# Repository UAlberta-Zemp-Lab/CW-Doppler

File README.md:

### Continuous Wave Doppler
--- 
Code and board files for high voltage switch and Teensy firmware

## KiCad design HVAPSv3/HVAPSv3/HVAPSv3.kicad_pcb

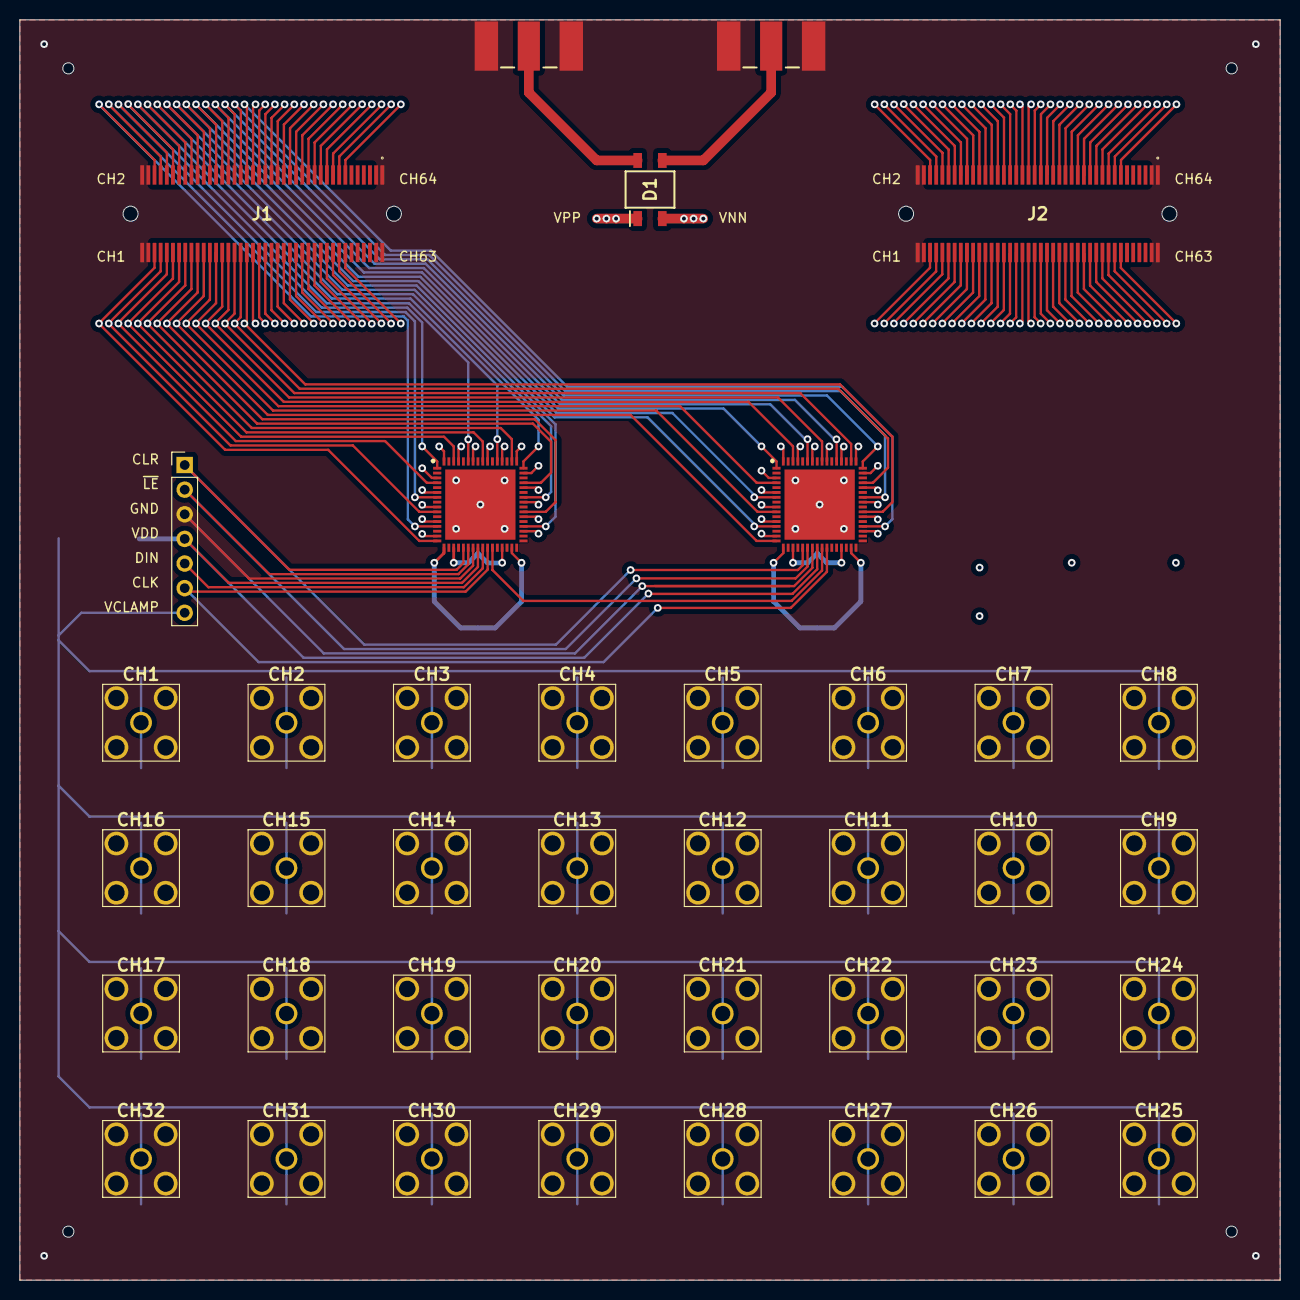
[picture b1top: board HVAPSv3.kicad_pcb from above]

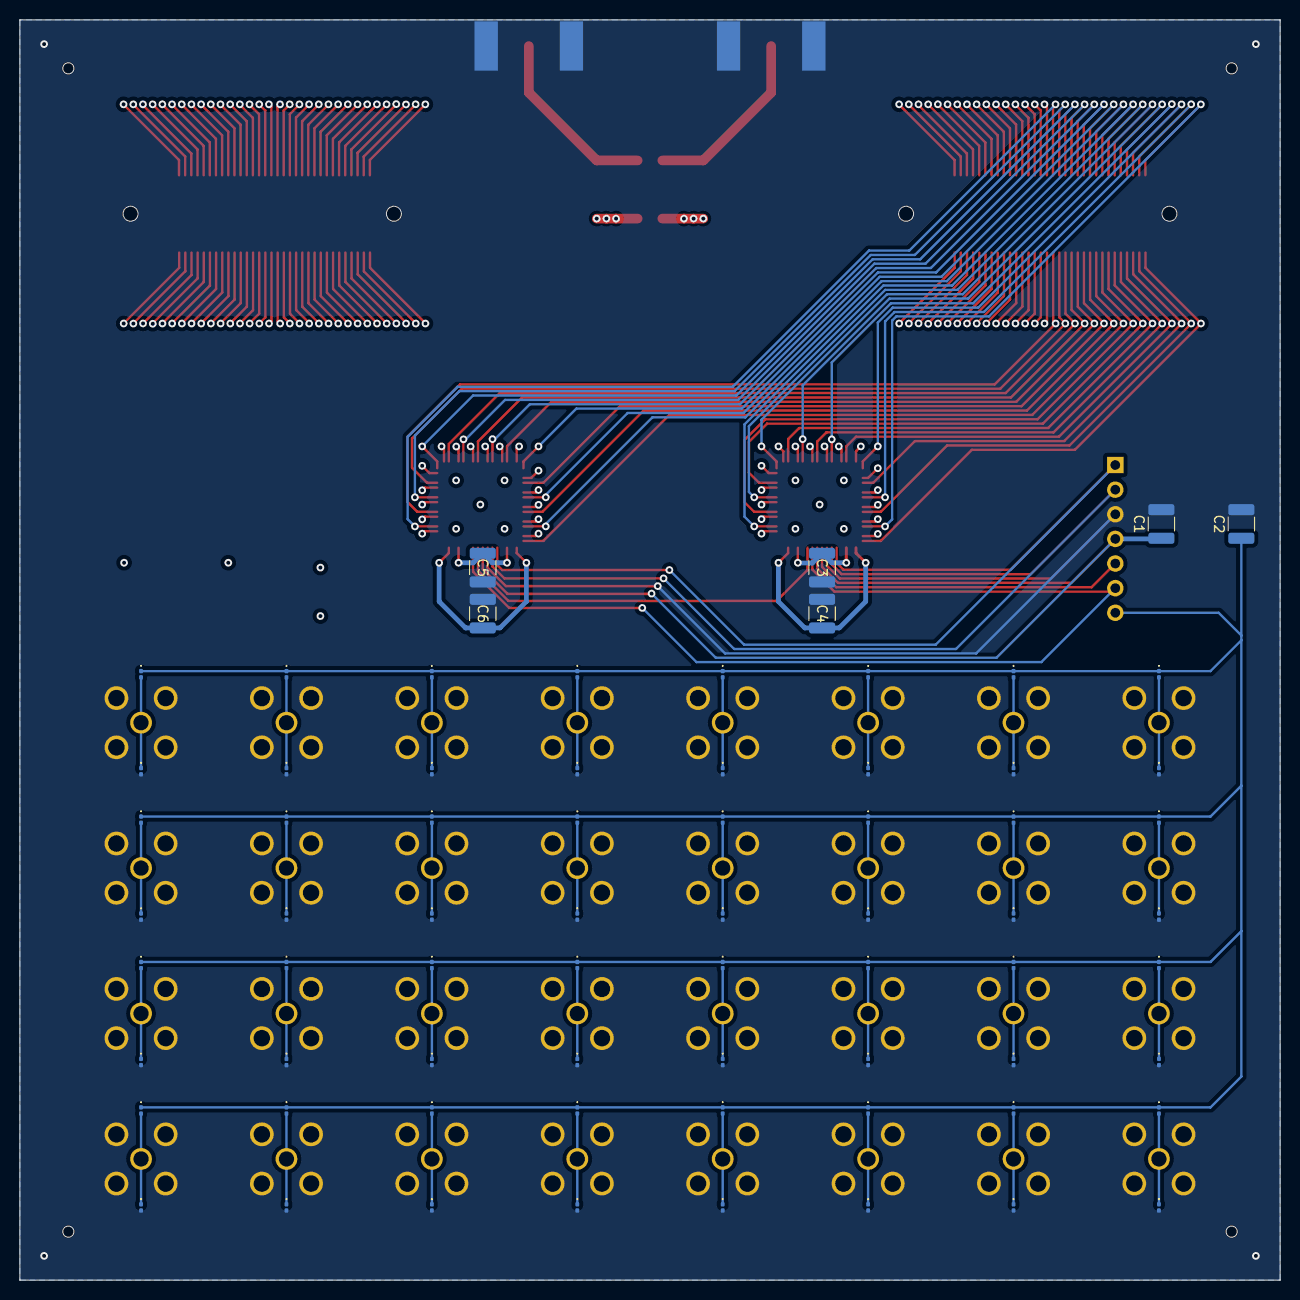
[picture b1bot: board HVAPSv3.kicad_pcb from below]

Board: 4 copper layers, 130.0 x 130.0 mm, 110 parts (70 on the bottom side), 108 nets.

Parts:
C1, C2: 1uF; C_1210_3225Metric
C3, C4, C5, C6: 0.22uF; C_1210_3225Metric
CH1, CH2, CH3, CH4, CH5, CH6, CH7, CH8, CH9, CH10, CH11, CH12, CH13, CH14, CH15, CH16, CH17, CH18, CH19, CH20, CH21, CH22, CH23, CH24, CH25, CH26, CH27, CH28, CH29, CH30, CH31, CH32: Conn_Coaxial; 1420701201
D1: D_Bridge_+A-A; HDS10M13
D2, D3, D4, D5, D6, D7, D8, D9, D10, D11, D12, D13, D14, D15, D16, D17, D18, D19, D20, D21, D22, D23, D24, D25, D26, D27, D28, D29, D30, D31, D32, D33, D34, D35, D36, D37, D38, D39, D40, D41, D42, D43, D44, D45, D46, D47, D48, D49, D50, D51, D52, D53, D54, D55, D56, D57, D58, D59, D60, D61, D62, D63, D64, D65: D_0201_0603Metric
IC1, IC2: HV2621_R4X; QFN50P900X900X100-65N-D
J1, J2: MEC6-140-02-L-D-RA1-TR; MEC6-140-02-X-D-RA1-TR
J3, J4: Conn_Coaxial_Power; 142-0701-851
J5: Conn_01x07_Socket; PinHeader_1x07_P2.54mm_Vertical

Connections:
/AFE1: CH1.1 (In), D8.2 (A), D9.1 (K), IC2.15 (SW0B)
/AFE2: CH2.1 (In), D16.2 (A), D17.1 (K), IC2.12 (SW1B)
/AFE3: CH3.1 (In), D24.2 (A), D25.1 (K), IC2.9 (SW2B)
/AFE4: CH4.1 (In), D32.2 (A), D33.1 (K), IC2.6 (SW3B)
/AFE5: CH5.1 (In), D40.2 (A), D41.1 (K), IC2.3 (SW4B)
/AFE6: CH6.1 (In), D48.2 (A), D49.1 (K), IC2.64 (SW5B)
/AFE7: CH7.1 (In), D56.2 (A), D57.1 (K), IC2.61 (SW6B)
/AFE8: CH8.1 (In), D64.2 (A), D65.1 (K), IC2.58 (SW7B)
/AFE9: CH9.1 (In), D6.2 (A), D7.1 (K), IC2.55 (SW8B)
/AFE10: CH10.1 (In), D14.2 (A), D15.1 (K), IC2.52 (SW9B)
/AFE11: CH11.1 (In), D22.2 (A), D23.1 (K), IC2.49 (SW10B)
/AFE12: CH12.1 (In), D30.2 (A), D31.1 (K), IC2.47 (SW11B)
/AFE13: CH13.1 (In), D38.2 (A), D39.1 (K), IC2.44 (SW12B)
/AFE14: CH14.1 (In), D46.2 (A), D47.1 (K), IC2.41 (SW13B)
/AFE15: CH15.1 (In), D54.2 (A), D55.1 (K), IC2.38 (SW14B)
/AFE16: CH16.1 (In), D62.2 (A), D63.1 (K), IC2.35 (SW15B)
/AFE17: CH17.1 (In), D4.2 (A), D5.1 (K), IC1.15 (SW0B)
/AFE18: CH18.1 (In), D12.2 (A), D13.1 (K), IC1.12 (SW1B)
/AFE19: CH19.1 (In), D20.2 (A), D21.1 (K), IC1.9 (SW2B)
/AFE20: CH20.1 (In), D28.2 (A), D29.1 (K), IC1.6 (SW3B)
/AFE21: CH21.1 (In), D36.2 (A), D37.1 (K), IC1.3 (SW4B)
/AFE22: CH22.1 (In), D44.2 (A), D45.1 (K), IC1.64 (SW5B)
/AFE23: CH23.1 (In), D52.2 (A), D53.1 (K), IC1.61 (SW6B)
/AFE24: CH24.1 (In), D60.2 (A), D61.1 (K), IC1.58 (SW7B)
/AFE25: CH25.1 (In), D2.2 (A), D3.1 (K), IC1.55 (SW8B)
/AFE26: CH26.1 (In), D10.2 (A), D11.1 (K), IC1.52 (SW9B)
/AFE27: CH27.1 (In), D18.2 (A), D19.1 (K), IC1.49 (SW10B)
/AFE28: CH28.1 (In), D26.2 (A), D27.1 (K), IC1.47 (SW11B)
/AFE29: CH29.1 (In), D34.2 (A), D35.1 (K), IC1.44 (SW12B)
/AFE30: CH30.1 (In), D42.2 (A), D43.1 (K), IC1.41 (SW13B)
/AFE31: CH31.1 (In), D50.2 (A), D51.1 (K), IC1.38 (SW14B)
/AFE32: CH32.1 (In), D58.2 (A), D59.1 (K), IC1.35 (SW15B)
/CLK: IC1.26 (CLK), IC2.26 (CLK), J5.6
/CLR: IC1.21 (CLR), IC2.21 (CLR), J5.1
/DIN: IC2.25 (DIN), J5.5
/DOUT: IC1.25 (DIN), IC2.27 (DOUT)
/IN1: IC2.16 (SW0A), J1.76, J2.76
/IN2: IC2.13 (SW1A), J1.75, J2.75
/IN3: IC2.10 (SW2A), J1.74, J2.74
/IN4: IC2.7 (SW3A), J1.73, J2.73
/IN5: IC2.4 (SW4A), J1.72, J2.72
/IN6: IC2.1 (SW5A), J1.71, J2.71
/IN7: IC2.62 (SW6A), J1.70, J2.70
/IN8: IC2.59 (SW7A), J1.69, J2.69
/IN9: IC2.56 (SW8A), J1.68, J2.68
/IN10: IC2.53 (SW9A), J1.67, J2.67
/IN11: IC2.50 (SW10A), J1.66, J2.66
/IN12: IC2.48 (SW11A), J1.65, J2.65
/IN13: IC2.45 (SW12A), J1.64, J2.64
/IN14: IC2.42 (SW13A), J1.63, J2.63
/IN15: IC2.39 (SW14A), J1.62, J2.62
/IN16: IC2.36 (SW15A), J1.61, J2.61
/IN17: IC1.16 (SW0A), J1.60, J2.60
/IN18: IC1.13 (SW1A), J1.59, J2.59
/IN19: IC1.10 (SW2A), J1.58, J2.58
/IN20: IC1.7 (SW3A), J1.57, J2.57
/IN21: IC1.4 (SW4A), J1.56, J2.56
/IN22: IC1.1 (SW5A), J1.55, J2.55
/IN23: IC1.62 (SW6A), J1.54, J2.54
/IN24: IC1.59 (SW7A), J1.53, J2.53
/IN25: IC1.56 (SW8A), J1.52, J2.52
/IN26: IC1.53 (SW9A), J1.51, J2.51
/IN27: IC1.50 (SW10A), J1.50, J2.50
/IN28: IC1.48 (SW11A), J1.49, J2.49
/IN29: IC1.45 (SW12A), J1.48, J2.48
/IN30: IC1.42 (SW13A), J1.47, J2.47
/IN31: IC1.39 (SW14A), J1.46, J2.46
/IN32: IC1.36 (SW15A), J1.45, J2.45
/IN33: J1.44, J2.44
/IN34: J1.43, J2.43
/IN35: J1.42, J2.42
/IN36: J1.41, J2.41
/IN37: J1.40, J2.40
/IN38: J1.39, J2.39
/IN39: J1.38, J2.38
/IN40: J1.37, J2.37
/IN41: J1.36, J2.36
/IN42: J1.35, J2.35
/IN43: J1.34, J2.34
/IN44: J1.33, J2.33
/IN45: J1.32, J2.32
/IN46: J1.31, J2.31
/IN47: J1.30, J2.30
/IN48: J1.29, J2.29
/IN49: J1.28, J2.28
/IN50: J1.27, J2.27
/IN51: J1.26, J2.26
/IN52: J1.25, J2.25
/IN53: J1.24, J2.24
/IN54: J1.23, J2.23
/IN55: J1.22, J2.22
/IN56: J1.21, J2.21
/IN57: J1.20, J2.20
/IN58: J1.19, J2.19
/IN59: J1.18, J2.18
/IN60: J1.17, J2.17
/IN61: J1.16, J2.16
/IN62: J1.15, J2.15
/IN63: J1.14, J2.14
/IN64: J1.13, J2.13
/VCLAMP: C2.1, D2.1 (K), D4.1 (K), D6.1 (K), D8.1 (K), D10.1 (K), D12.1 (K), D14.1 (K), D16.1 (K), D18.1 (K), D20.1 (K), D22.1 (K), D24.1 (K), D26.1 (K), D28.1 (K), D30.1 (K), D32.1 (K), D34.1 (K), D36.1 (K), D38.1 (K), D40.1 (K), D42.1 (K), D44.1 (K), D46.1 (K), D48.1 (K), D50.1 (K), D52.1 (K), D54.1 (K), D56.1 (K), D58.1 (K), D60.1 (K), D62.1 (K), D64.1 (K), J5.7
/~LE: IC1.22 (~LE), IC2.22 (~LE), J5.2
GND: C1.2, C2.2, C3.2, C4.2, C5.2, C6.2, CH1.2 (Ext), CH2.2 (Ext), CH3.2 (Ext), CH4.2 (Ext), CH5.2 (Ext), CH6.2 (Ext), CH7.2 (Ext), CH8.2 (Ext), CH9.2 (Ext), CH10.2 (Ext), CH11.2 (Ext), CH12.2 (Ext), CH13.2 (Ext), CH14.2 (Ext), CH15.2 (Ext), CH16.2 (Ext), CH17.2 (Ext), CH18.2 (Ext), CH19.2 (Ext), CH20.2 (Ext), CH21.2 (Ext), CH22.2 (Ext), CH23.2 (Ext), CH24.2 (Ext), CH25.2 (Ext), CH26.2 (Ext), CH27.2 (Ext), CH28.2 (Ext), CH29.2 (Ext), CH30.2 (Ext), CH31.2 (Ext), CH32.2 (Ext), D3.2 (A), D5.2 (A), D7.2 (A), D9.2 (A), D11.2 (A), D13.2 (A), D15.2 (A), D17.2 (A), D19.2 (A), D21.2 (A), D23.2 (A), D25.2 (A), D27.2 (A), D29.2 (A), D31.2 (A), D33.2 (A), D35.2 (A), D37.2 (A), D39.2 (A), D41.2 (A), D43.2 (A), D45.2 (A), D47.2 (A), D49.2 (A), D51.2 (A), D53.2 (A), D55.2 (A), D57.2 (A), D59.2 (A), D61.2 (A), D63.2 (A), D65.2 (A), IC1.23 (GND), IC2.23 (GND), J1.1, J1.2, J1.3, J1.4, J1.77, J1.78, J1.79, J1.80, J2.1, J2.2, J2.3, J2.4, J2.77, J2.78, J2.79, J2.80, J3.2 (Ext), J4.2 (Ext), J5.3
unnamed: D1.4, J3.1 (In)
unnamed: D1.2, J4.1 (In)
VDD: C1.1, IC1.24 (VDD), IC2.24 (VDD), J5.4
VNN: C4.1, C6.1, D1.3 (-), IC1.17 (VNN_1), IC1.31 (VNN_2), IC1.65 (VSUB), IC2.17 (VNN_1), IC2.31 (VNN_2), IC2.65 (VSUB)
VPP: C3.1, C5.1, D1.1 (+), IC1.19 (VPP_1), IC1.29 (VPP_2), IC2.19 (VPP_1), IC2.29 (VPP_2)

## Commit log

2023-08-29 Initial Commit: Added firmware and MATLAB code
2023-08-30 added board files
2023-08-30 changed Position class to Vector class
